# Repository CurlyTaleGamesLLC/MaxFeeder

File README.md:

# Max Feeder

<video autoplay loop muted src="https://user-images.githubusercontent.com/25337335/216802715-1deb94b0-7a2f-4627-93f5-1e41935b5955.mp4">
</video>

## Part Feeding Simplified
### Designed to automate feeding parts for your Open PnP compatible pick and place machine
<br/>

This feeder is designed to be set up as an AutoFeeder in OpenPNP. It easily clips to 2020 aluminum extrusion and uses an Arduino Mega to receive Gcode commands sent over a USB serial connection in Open PnP. The Max Feeder Shield can control up to 34 feeders.

The design of the Max Feeder is based on [the 0816 feeder design from mgrl.](https://docs.mgrl.de/maschine:pickandplace:feeder:0816feeder) However after two years of development I redesigned every piece of it to improve and simplify the feeder as much as possible.

During development, I also referenced the remix of the 0816 feeder made Nicmoly for the Lumen PNP.

<br/>

# Where can I get a Max Feeder?

[I am selling kits of the Max Feeder Shield and kits of 5x 8mm Max Feeders.](https://store.curlytalegames.com/pages/max-feeders)
> The online store is now live! Thanks for supporting this open hardware project!

This is an Open Hardware project, so all of the design files and the BOM are included in this repo as well.

[If you like what I'm doing consider becoming a Github Sponsor :gift_heart:](https://github.com/sponsors/CurlyTaleGames)

<br/>

# Hardware

## Max Feeder Shield
- 1 - Max Feeder Shield PCB
- 34 - 4 Pin 2.54mm JST connectors
- 1 - Arduino Mega
- 1 - 10uf Capacitor
- 1 - Barrel Jack
- 1 - 3.81mm Screw Terminal - Optional
- 1 - 6mm Through Hole Tacticle Switch
- 1 - 5v DC 3A (or more) Power Supply
- LOTS of 2.54mm Male Header
- Mounting Bracket in the "3D" folder

<br/>

## Max Feeder
- 1 - Max Feeder PCB
- 3D printed files in the "3D" folder
- 5 - [M3 6mm screws](https://www.amazon.com/Alloy-Steel-Socket-Screws-Black/dp/B00W8YSCIS/)
- 1 - [4 Pin 2.54mm JST cables 100cm in length ("stepper motor cable")](https://www.amazon.com/Wires-Motor-XH2-54-4P-PH2-0-6P-Printers-Accessories%EF%BC%8C3D/dp/B08PV6XGK2/)
- 3 - [M3 20mm screws](https://www.amazon.com/Prime-Line-9180478-Socket-Screws-10-Pack/dp/B07D5S3154/)
- 1 - [SPDT Limit Switch](https://www.amazon.com/dp/B088W8WMTB)
- 1 - [1N4001 Diode](https://www.amazon.com/MCIGICM-Rectifier-Electronic-Silicon-Doorbell/dp/B071YWNBVM/)
- 1 - [5 pin 2.54mm Angled Male Header](https://www.amazon.com/Antrader-2-54mm-Right-Header-Connector/dp/B07M88GRHG/)
- 1 - [2 pin 2.54mm Female header cable](https://www.amazon.com/Mayata-Female-Jumper-Dupont-Printer/dp/B07H1WDN3R/) or [Female to Female Dupont cables](https://www.amazon.com/EDGELEC-Breadboard-1pin-1pin-Connector-Multicolored/dp/B07GCZVCGS/)
- 1 - [N20 Geared DC Motor 60 RPM](https://www.aliexpress.com/item/3256803042731079.html?pdp_ext_f=%7B"sku_id":"12000024757391447"%7D)
- 1 - [MG90S Servo 180 degree](https://www.amazon.com/Compatible-Raspberry-Project-Helicopter-Airplane/dp/B0925V3X2S/)
- 1 - [M2 14mm dowel pin](https://www.amazon.com/MroMax-2-5x14mm-Stainless-Rust-Proof-Elements/dp/B07ZF4X7VQ/) or [2mm diameter rod cut to 14mm in length](https://www.amazon.com/dp/B0962RMLVJ)
- [Replacement Pen Springs](https://www.amazon.com/dp/B089JYV7BT)
- [Latex Free Orthodontic Elastics](https://www.amazon.com/dp/B08NCK1K6P)

<br/>

# 3D Prints

## Max Feeder

Included are two 3MF files which has all the parts oriented and ready to print. Also there are the individual STL files if your slicer doesn't support 3MF files.

The files that need to be printed with a 0.4mm nozzle are labeled, all the other parts can be printed with 0.4mm, 0.6mm, or 0.8mm nozzles. Everything is designed to be printed without supports. If you print with a 0.8mm nozzle you can print a whole feeder in less than 1.5 hours.

[Download the 8mm Max Feeder.](/3D/8mm/) [12mm](/3D/12mm/), [16mm](/3D/16mm/), and [24mm](/3D/24mm/) versions are available in beta status. All of the feeder widths use the same hardware. The only difference between them are the 3D print files.

### Multiple Mounting Options

`FeederBase.stl` and `FeederCover.stl` are designed to clip onto 2020 aluminum extrusion. This is the default configuration of the Max Feeder and it's designed to mount to the Lumen PnP.

`DIN-FeederBase.stl` and `DIN-FeederCover.stl` are designed to clip onto DIN Rail for pick and place machines with a flat mounting surface, like the LitePlacer.

`2040-FeederBase.stl` and `2040-FeederCover.stl` are designed to clip onto 2040 aluminum extrusion. So it will mount to any pick and place machines that the original 0816 feeder can mount to.

<br/>

## Max Feeder Shield

Included is a bracket to bolt a Max Feeder Shield + Arduino Mega compatible microcontroller to the side of some 2020 aluminum extrusion. The current bracket was designed to be used with a Lumen PNP but might work for other pick and place machines too.

[Download it here](/3D/Bracket/)

<br/>

# Feeder Assembly & Configuration

- [Uploading Firmware](./Docs/firmware.md)
- [Max Feeder PCB Assembly](./Docs/pcb.md)
- [Servo Poker Assembly](./Docs/poker.md)
- [Tape Gear Motor Assembly](./Docs/motor.md)
- [Final Feeder Assembly](./Docs/finishing-assembly.md)
- [Open PnP AutoFeeder Configuration](./Docs/openpnp.md)
- [Loading and Unloading Tape into Max Feeder](./Docs/finishing-assembly.md)

<br/>

## Reel Holder

[Download and print this reel holder for your spools of parts](https://www.printables.com/model/343598-smd-reel-holder-for-pick-and-place-machine)

## Troubleshooting

If you are still having problems after going through the "Feeder Assembly & Configuration" [here are some solutions to common problems](./Docs/troubleshooting.md)

## Notes

There are a few optional parts for the feeder you can print.

### QR Code Cap

This part is attached to the front of your feeder and is designed to have a 1/2" x 1/2" QR code stuck onto it. [Atanisoft](https://github.com/atanisoft) and I have been working on [FeederUtils](https://github.com/atanisoft/FeederUtils), which features a way to import and automatically set up part feeders in Open PnP. The QR code portion of the project is still under development.

[Check it out here](https://github.com/atanisoft/FeederUtils)

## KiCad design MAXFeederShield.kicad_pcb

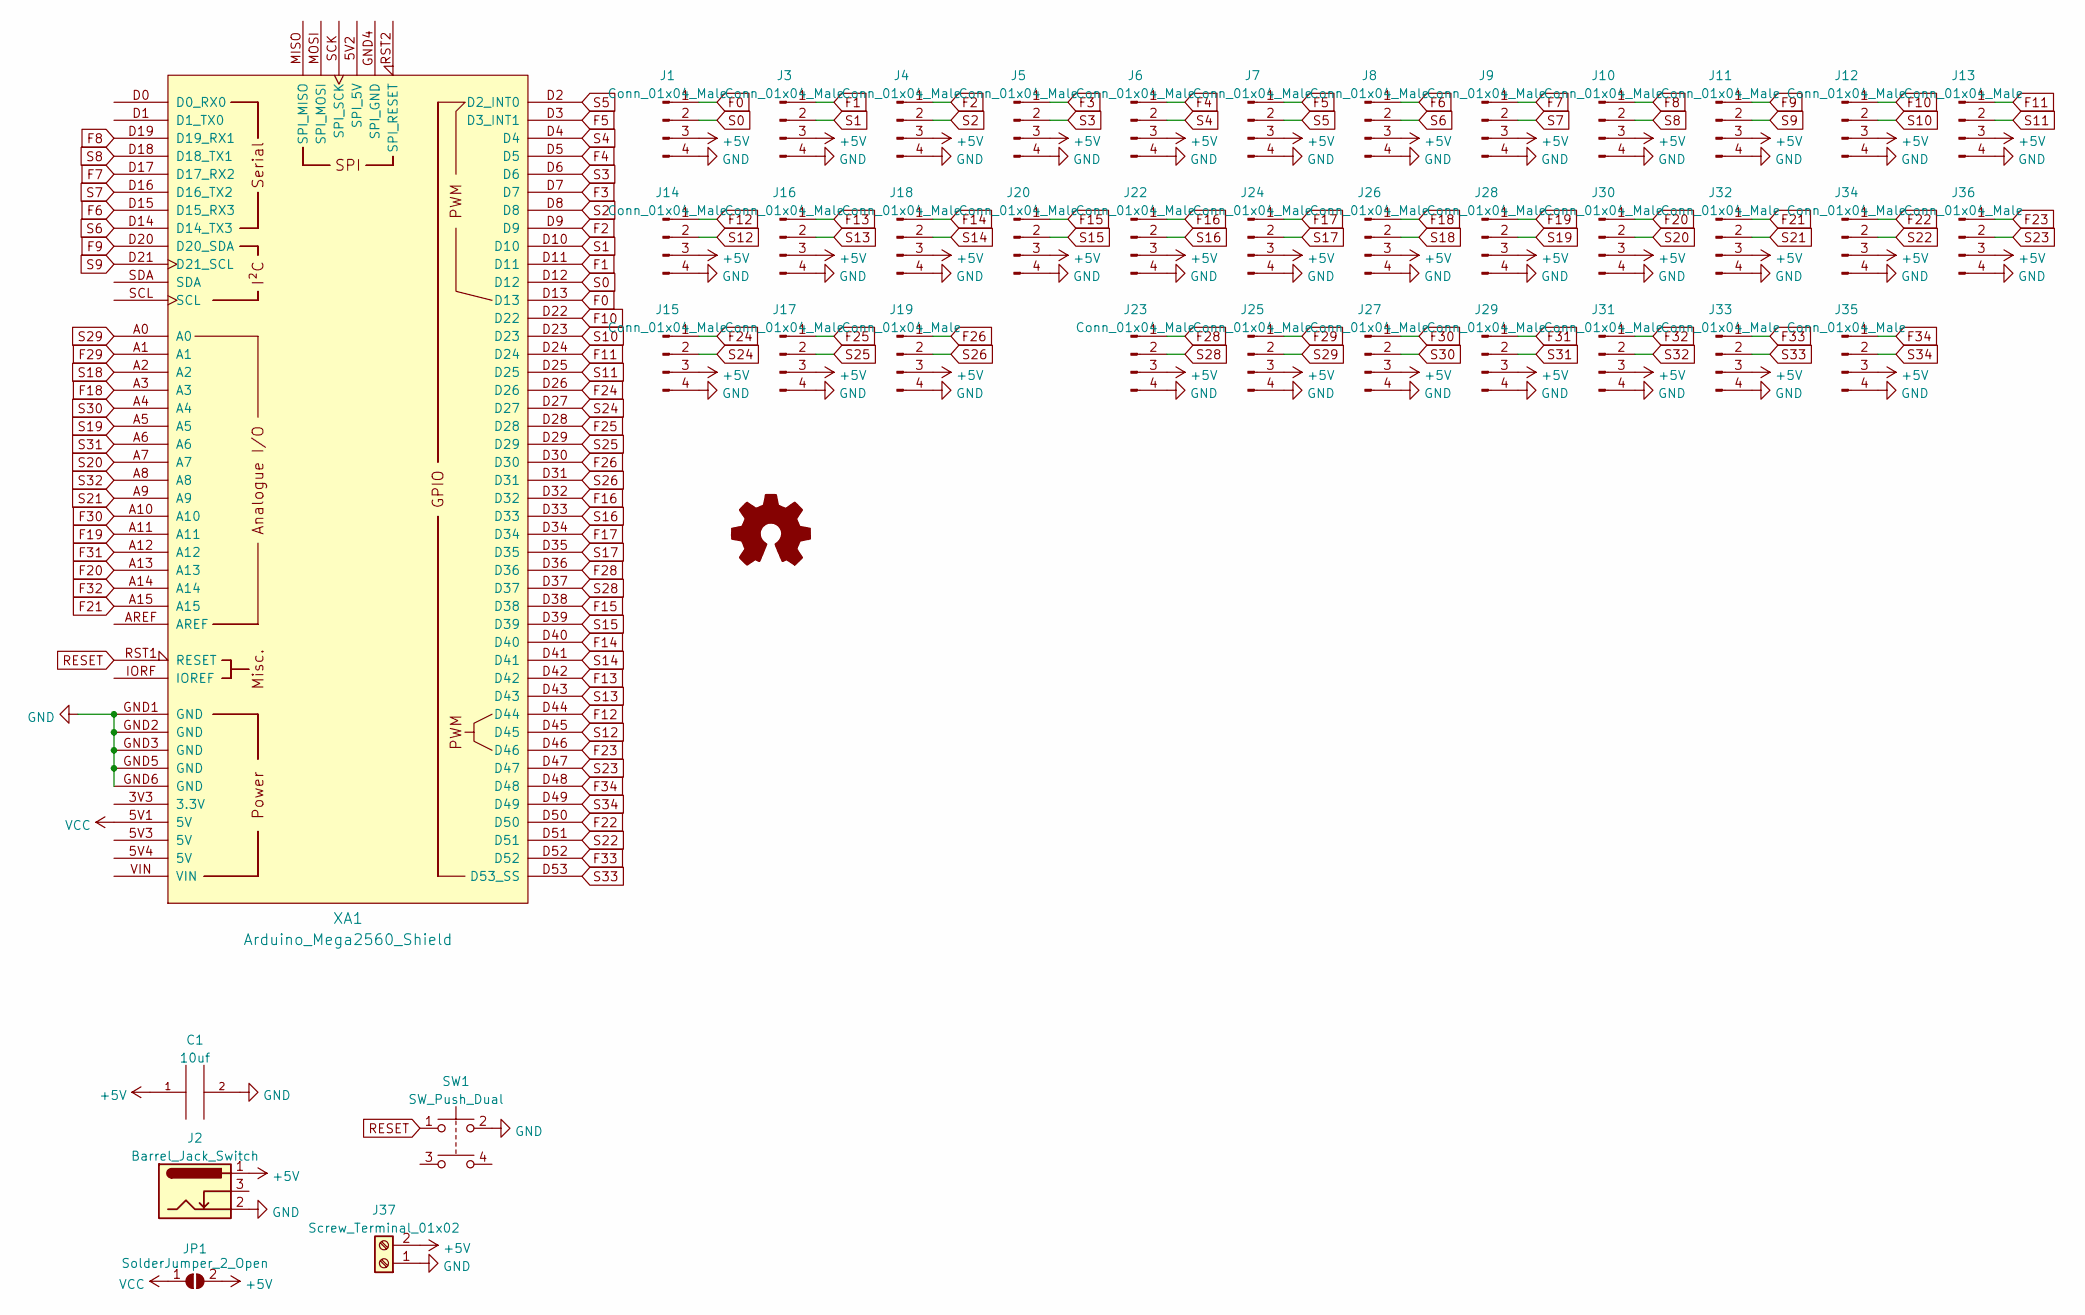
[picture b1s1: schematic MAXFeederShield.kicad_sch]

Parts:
C1: 10uf; CP_Radial_D5.0mm_P2.50mm
J1, J3, J4, J5, J6, J7, J8, J9, J10, J11, J12, J13, J14, J15, J16, J17, J18, J19, J20, J22, J23, J24, J25, J26, J27, J28, J29, J30, J31, J32, J33, J34, J35, J36: Conn_01x04_Male; JST_EH_B4B-EH-A_1x04_P2.50mm_Vertical_LOCKING
J2: Barrel_Jack_Switch; BarrelJack_Horizontal
J37: Screw_Terminal_01x02; PhoenixContact_MC_1,5_2-G-3.81_1x02_P3.81mm_Horizontal
JP1: SolderJumper_2_Open; SolderJumper-2_P1.3mm_Open_Pad1.0x1.5mm
SW1: SW_Push_Dual; SW_PUSH_6mm
XA1: Arduino_Mega2560_Shield; Arduino_Mega2560_Shield_NO_HOLES

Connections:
+5V: C1.1, J1.3, J2.1, J3.3, J4.3, J5.3, J6.3, J7.3, J8.3, J9.3, J10.3, J11.3, J12.3, J13.3, J14.3, J15.3, J16.3, J17.3, J18.3, J19.3, J20.3, J22.3, J23.3, J24.3, J25.3, J26.3, J27.3, J28.3, J29.3, J30.3, J31.3, J32.3, J33.3, J34.3, J35.3, J36.3, J37.2, JP1.2 (B)
F0: J1.1, XA1.D13
F1: J3.1, XA1.D11
F2: J4.1, XA1.D9
F3: J5.1, XA1.D7
F4: J6.1, XA1.D5
F5: J7.1, XA1.D3 (D3_INT1)
F6: J8.1, XA1.D15 (D15_RX3)
F7: J9.1, XA1.D17 (D17_RX2)
F8: J10.1, XA1.D19 (D19_RX1)
F9: J11.1, XA1.D20 (D20_SDA)
F10: J12.1, XA1.D22
F11: J13.1, XA1.D24
F12: J14.1, XA1.D44
F13: J16.1, XA1.D42
F14: J18.1, XA1.D40
F15: J20.1, XA1.D38
F16: J22.1, XA1.D32
F17: J24.1, XA1.D34
F18: J26.1, XA1.A3
F19: J28.1, XA1.A11
F20: J30.1, XA1.A13
F21: J32.1, XA1.A15
F22: J34.1, XA1.D50
F23: J36.1, XA1.D46
F24: J15.1, XA1.D26
F25: J17.1, XA1.D28
F26: J19.1, XA1.D30
F28: J23.1, XA1.D36
F29: J25.1, XA1.A1
F30: J27.1, XA1.A10
F31: J29.1, XA1.A12
F32: J31.1, XA1.A14
F33: J33.1, XA1.D52
F34: J35.1, XA1.D48
GND: C1.2, J1.4, J2.2, J3.4, J4.4, J5.4, J6.4, J7.4, J8.4, J9.4, J10.4, J11.4, J12.4, J13.4, J14.4, J15.4, J16.4, J17.4, J18.4, J19.4, J20.4, J22.4, J23.4, J24.4, J25.4, J26.4, J27.4, J28.4, J29.4, J30.4, J31.4, J32.4, J33.4, J34.4, J35.4, J36.4, J37.1, SW1.2, XA1.GND1 (GND), XA1.GND2 (GND), XA1.GND3 (GND), XA1.GND5 (GND), XA1.GND6 (GND)
RESET: SW1.1, XA1.RST1 (RESET)
S0: J1.2, XA1.D12
S1: J3.2, XA1.D10
S2: J4.2, XA1.D8
S3: J5.2, XA1.D6
S4: J6.2, XA1.D4
S5: J7.2, XA1.D2 (D2_INT0)
S6: J8.2, XA1.D14 (D14_TX3)
S7: J9.2, XA1.D16 (D16_TX2)
S8: J10.2, XA1.D18 (D18_TX1)
S9: J11.2, XA1.D21 (D21_SCL)
S10: J12.2, XA1.D23
S11: J13.2, XA1.D25
S12: J14.2, XA1.D45
S13: J16.2, XA1.D43
S14: J18.2, XA1.D41
S15: J20.2, XA1.D39
S16: J22.2, XA1.D33
S17: J24.2, XA1.D35
S18: J26.2, XA1.A2
S19: J28.2, XA1.A5
S20: J30.2, XA1.A7
S21: J32.2, XA1.A9
S22: J34.2, XA1.D51
S23: J36.2, XA1.D47
S24: J15.2, XA1.D27
S25: J17.2, XA1.D29
S26: J19.2, XA1.D31
S28: J23.2, XA1.D37
S29: J25.2, XA1.A0
S30: J27.2, XA1.A4
S31: J29.2, XA1.A6
S32: J31.2, XA1.A8
S33: J33.2, XA1.D53 (D53_SS)
S34: J35.2, XA1.D49
VCC: JP1.1 (A), XA1.5V1 (5V)

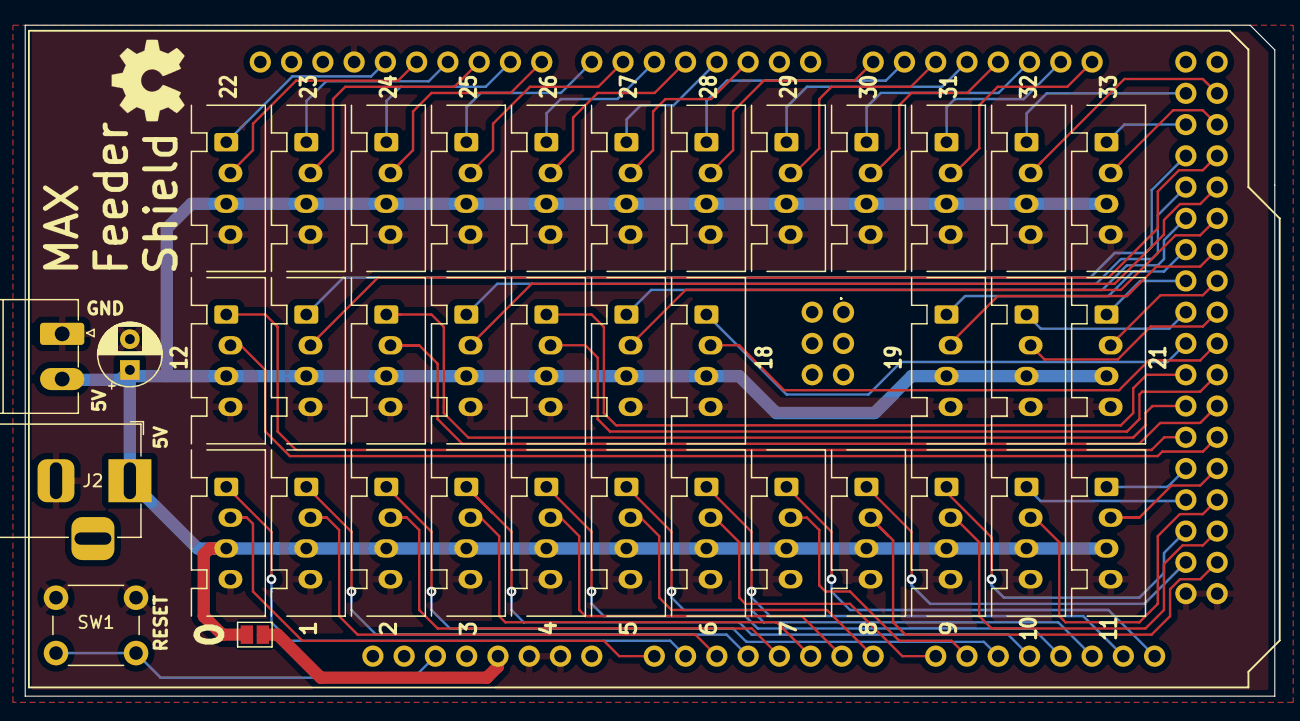
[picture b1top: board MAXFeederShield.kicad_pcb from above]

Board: 2 copper layers, 101.5 x 54.5 mm, 40 parts (0 on the bottom side), 72 nets.

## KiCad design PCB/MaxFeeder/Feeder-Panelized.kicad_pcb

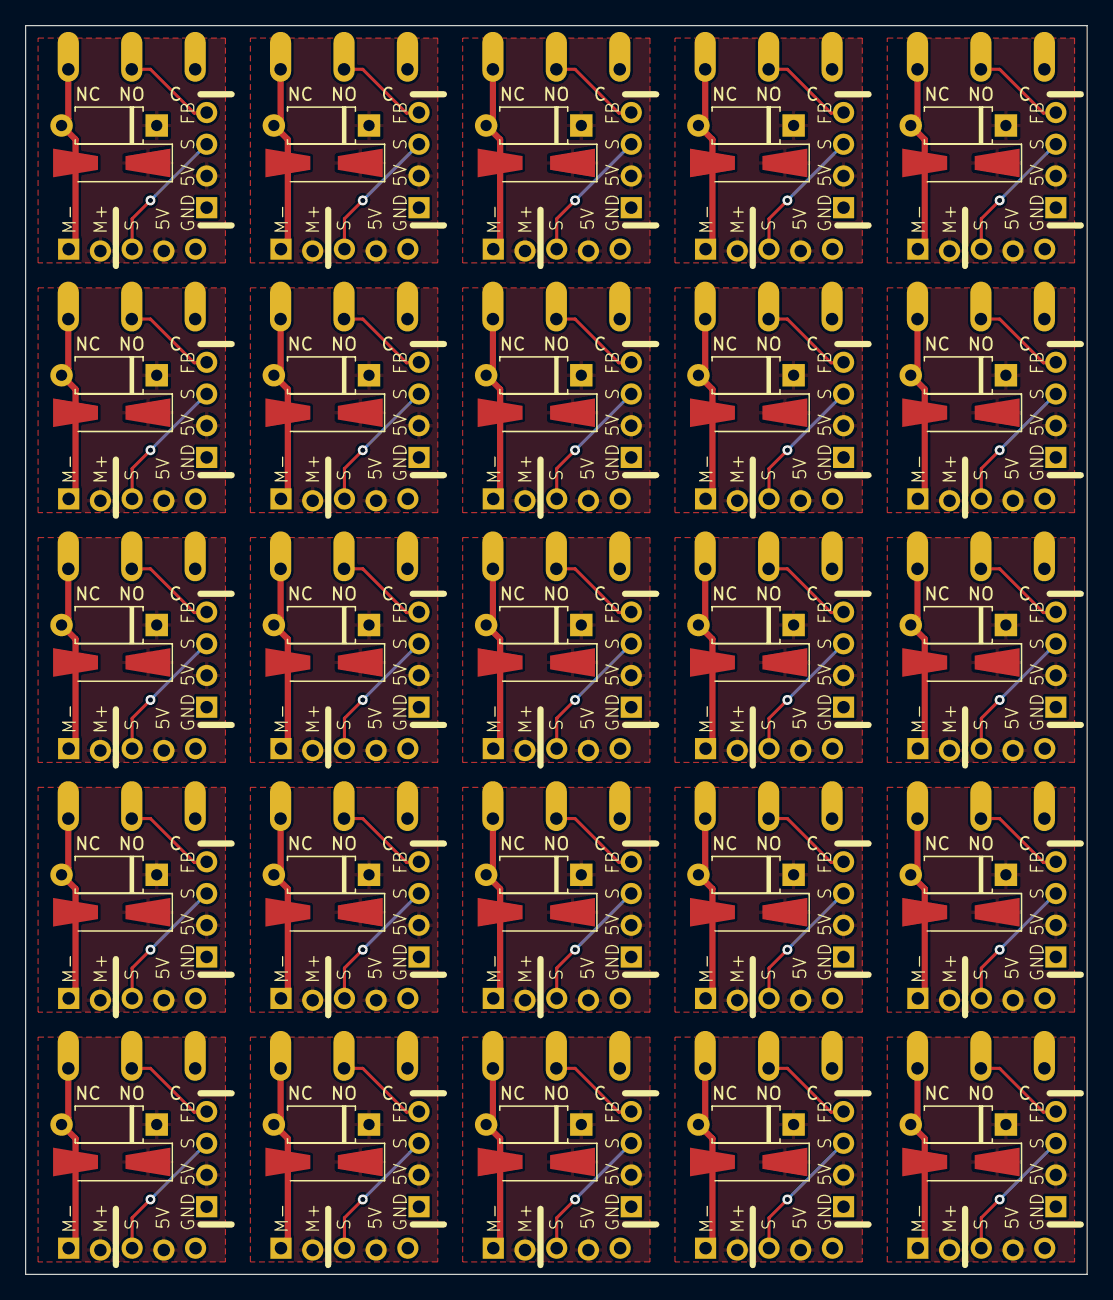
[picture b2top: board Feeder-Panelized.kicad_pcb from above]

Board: 2 copper layers, 85.0 x 100.0 mm, 125 parts (0 on the bottom side), 5 nets.

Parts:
D1, D3, D5, D7, D9, D11, D13, D15, D17, D19, D21, D23, D25, D27, D29, D31, D33, D35, D37, D39, D41, D43, D45, D47, D49: 1N4001; D_SMA-SMB_Universal_Handsoldering
D2, D4, D6, D8, D10, D12, D14, D16, D18, D20, D22, D24, D26, D28, D30, D32, D34, D36, D38, D40, D42, D44, D46, D48, D50: 1N4001; D_A-405_P7.62mm_Horizontal
J1, J2, J3, J7, J9, J11, J13, J15, J17, J19, J21, J23, J25, J27, J29, J31, J33, J35, J37, J39, J41, J43, J45, J47, J49: Conn_01x05; PinSocket_1x05_P2.54mm_Vertical_Clean_Locking
J4, J5, J6, J8, J10, J12, J14, J16, J18, J20, J22, J24, J26, J28, J30, J32, J34, J36, J38, J40, J42, J44, J46, J48, J50: Conn_01x04; PinSocket_1x04_P2.54mm_Vertical_Clean
SW1, SW2, SW3, SW4, SW5, SW6, SW7, SW8, SW9, SW10, SW11, SW12, SW13, SW14, SW15, SW16, SW17, SW18, SW19, SW20, SW21, SW22, SW23, SW24, SW25: SW_SPDT; Microswitch

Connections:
+5V: D1.1 (K), D2.1 (K), D3.1 (K), D4.1 (K), D5.1 (K), D6.1 (K), D7.1 (K), D8.1 (K), D9.1 (K), D10.1 (K), D11.1 (K), D12.1 (K), D13.1 (K), D14.1 (K), D15.1 (K), D16.1 (K), D17.1 (K), D18.1 (K), D19.1 (K), D20.1 (K), D21.1 (K), D22.1 (K), D23.1 (K), D24.1 (K), D25.1 (K), D26.1 (K), D27.1 (K), D28.1 (K), D29.1 (K), D30.1 (K), D31.1 (K), D32.1 (K), D33.1 (K), D34.1 (K), D35.1 (K), D36.1 (K), D37.1 (K), D38.1 (K), D39.1 (K), D40.1 (K), D41.1 (K), D42.1 (K), D43.1 (K), D44.1 (K), D45.1 (K), D46.1 (K), D47.1 (K), D48.1 (K), D49.1 (K), D50.1 (K), J1.2, J1.4, J2.2, J2.4, J3.2, J3.4, J4.2, J5.2, J6.2, J7.2, J7.4, J8.2, J9.2, J9.4, J10.2, J11.2, J11.4, J12.2, J13.2, J13.4, J14.2, J15.2, J15.4, J16.2, J17.2, J17.4, J18.2, J19.2, J19.4, J20.2, J21.2, J21.4, J22.2, J23.2, J23.4, J24.2, J25.2, J25.4, J26.2, J27.2, J27.4, J28.2, J29.2, J29.4, J30.2, J31.2, J31.4, J32.2, J33.2, J33.4, J34.2, J35.2, J35.4, J36.2, J37.2, J37.4, J38.2, J39.2, J39.4, J40.2, J41.2, J41.4, J42.2, J43.2, J43.4, J44.2, J45.2, J45.4, J46.2, J47.2, J47.4, J48.2, J49.2, J49.4, J50.2
/FEEDBACK: J4.4, J5.4, J6.4, J8.4, J10.4, J12.4, J14.4, J16.4, J18.4, J20.4, J22.4, J24.4, J26.4, J28.4, J30.4, J32.4, J34.4, J36.4, J38.4, J40.4, J42.4, J44.4, J46.4, J48.4, J50.4, SW1.3 (C), SW2.3 (C), SW3.3 (C), SW4.3 (C), SW5.3 (C), SW6.3 (C), SW7.3 (C), SW8.3 (C), SW9.3 (C), SW10.3 (C), SW11.3 (C), SW12.3 (C), SW13.3 (C), SW14.3 (C), SW15.3 (C), SW16.3 (C), SW17.3 (C), SW18.3 (C), SW19.3 (C), SW20.3 (C), SW21.3 (C), SW22.3 (C), SW23.3 (C), SW24.3 (C), SW25.3 (C)
/N20-GND: D1.2 (A), D2.2 (A), D3.2 (A), D4.2 (A), D5.2 (A), D6.2 (A), D7.2 (A), D8.2 (A), D9.2 (A), D10.2 (A), D11.2 (A), D12.2 (A), D13.2 (A), D14.2 (A), D15.2 (A), D16.2 (A), D17.2 (A), D18.2 (A), D19.2 (A), D20.2 (A), D21.2 (A), D22.2 (A), D23.2 (A), D24.2 (A), D25.2 (A), D26.2 (A), D27.2 (A), D28.2 (A), D29.2 (A), D30.2 (A), D31.2 (A), D32.2 (A), D33.2 (A), D34.2 (A), D35.2 (A), D36.2 (A), D37.2 (A), D38.2 (A), D39.2 (A), D40.2 (A), D41.2 (A), D42.2 (A), D43.2 (A), D44.2 (A), D45.2 (A), D46.2 (A), D47.2 (A), D48.2 (A), D49.2 (A), D50.2 (A), J1.1, J2.1, J3.1, J7.1, J9.1, J11.1, J13.1, J15.1, J17.1, J19.1, J21.1, J23.1, J25.1, J27.1, J29.1, J31.1, J33.1, J35.1, J37.1, J39.1, J41.1, J43.1, J45.1, J47.1, J49.1, SW1.1 (A), SW2.1 (A), SW3.1 (A), SW4.1 (A), SW5.1 (A), SW6.1 (A), SW7.1 (A), SW8.1 (A), SW9.1 (A), SW10.1 (A), SW11.1 (A), SW12.1 (A), SW13.1 (A), SW14.1 (A), SW15.1 (A), SW16.1 (A), SW17.1 (A), SW18.1 (A), SW19.1 (A), SW20.1 (A), SW21.1 (A), SW22.1 (A), SW23.1 (A), SW24.1 (A), SW25.1 (A)
/SERVO: J1.3, J2.3, J3.3, J4.3, J5.3, J6.3, J7.3, J8.3, J9.3, J10.3, J11.3, J12.3, J13.3, J14.3, J15.3, J16.3, J17.3, J18.3, J19.3, J20.3, J21.3, J22.3, J23.3, J24.3, J25.3, J26.3, J27.3, J28.3, J29.3, J30.3, J31.3, J32.3, J33.3, J34.3, J35.3, J36.3, J37.3, J38.3, J39.3, J40.3, J41.3, J42.3, J43.3, J44.3, J45.3, J46.3, J47.3, J48.3, J49.3, J50.3
GND: J1.5, J2.5, J3.5, J4.1, J5.1, J6.1, J7.5, J8.1, J9.5, J10.1, J11.5, J12.1, J13.5, J14.1, J15.5, J16.1, J17.5, J18.1, J19.5, J20.1, J21.5, J22.1, J23.5, J24.1, J25.5, J26.1, J27.5, J28.1, J29.5, J30.1, J31.5, J32.1, J33.5, J34.1, J35.5, J36.1, J37.5, J38.1, J39.5, J40.1, J41.5, J42.1, J43.5, J44.1, J45.5, J46.1, J47.5, J48.1, J49.5, J50.1, SW1.2 (B), SW2.2 (B), SW3.2 (B), SW4.2 (B), SW5.2 (B), SW6.2 (B), SW7.2 (B), SW8.2 (B), SW9.2 (B), SW10.2 (B), SW11.2 (B), SW12.2 (B), SW13.2 (B), SW14.2 (B), SW15.2 (B), SW16.2 (B), SW17.2 (B), SW18.2 (B), SW19.2 (B), SW20.2 (B), SW21.2 (B), SW22.2 (B), SW23.2 (B), SW24.2 (B), SW25.2 (B)

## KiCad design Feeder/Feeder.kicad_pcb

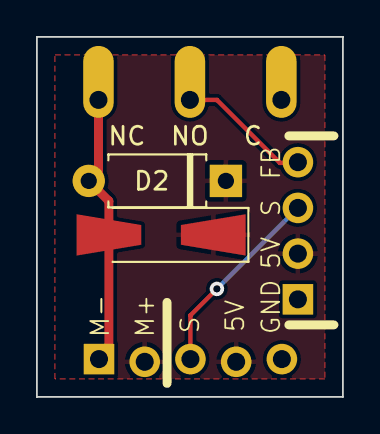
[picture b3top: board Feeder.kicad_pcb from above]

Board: 2 copper layers, 17.0 x 20.0 mm, 5 parts (0 on the bottom side), 5 nets.

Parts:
D1: 1N4001; D_SMA-SMB_Universal_Handsoldering
D2: 1N4001; D_A-405_P7.62mm_Horizontal
J1: Conn_01x05; PinSocket_1x05_P2.54mm_Vertical_Clean_Locking
J4: Conn_01x04; PinSocket_1x04_P2.54mm_Vertical_Clean
SW1: SW_SPDT; Microswitch

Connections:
+5V: D1.1 (K), D2.1 (K), J1.2, J1.4, J4.2
/FEEDBACK: J4.4, SW1.3 (C)
/N20-GND: D1.2 (A), D2.2 (A), J1.1, SW1.1 (A)
/SERVO: J1.3, J4.3
GND: J1.5, J4.1, SW1.2 (B)

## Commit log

2022-05-19 hello world!
2022-07-01 Redesigned shield PCB, as well as adapter PCB, modified 0816 feeder firmware
2022-07-01 fixed some file names and updated readme
2022-07-12 tweaked pad size on PCB and added 3d files for 8mm feeder
2022-07-12 fixed 3d model, updated docs
2022-07-14 added correct 3d gear part, added pictures, and fixed typo
2022-07-17 updated feeder design and documentation
2022-07-19 added 0.1mm to gear axle diameter thinned QR mounting point to snap on, and added links to docs
2022-11-20 removed need for M610 S1 command, auto detach servos
2023-01-18 updated 3d files, updated docs, added validation script
2023-01-18 added bracket step file
2023-01-30 Added more clearance for thicker 8mm paper tape, and adjusted leaf spring to also work better with thinner plastic tapes
2023-02-02 added updated documentation - updated max feeder shield bracket
2023-02-02 typo, added video
2023-02-04 fixed docs, updated leaf spring
2023-02-05 added docs for open pnp
2023-02-05 updated front page readme, added error regex
2023-02-05 added notes to readme
2023-03-28 launched online store
2023-04-16 added beta 12mm feeders and added pro tip to motor gears
2023-09-11 python script to test the feeders
2023-09-11 fix the window title
2023-09-11 fix the script to support 34 feeders
2023-09-12 add keyboard shortkut function and F value for each feeder controlled
2023-09-12 deleting keyboar assignation on second click
2023-09-12 key not monitored when the app is not in focus
2023-09-12 add readme
2023-09-12 add the port name in the serial status label add serial open condition for writing and listening
2023-11-05 Added PCB poker tip, added 8-24mm feeder widths, updated docs, cleaned up repo
2023-11-05 added reel holder link
2023-11-05 added photo of pcb poker tips
2023-11-07 forgot to include the washer in the plate, updated the 24mm base leaf spring to have more contact with bed
2023-11-16 added support for DIN rail mounted feeders for liteplacer. Updated leaf spring for more reliable printing
2023-12-03 added 2040 max feeder version, fixed hole diameter in base, thicker leaf spring to easier printing
2024-02-10 removed unique part number silk screen on diodes
2025-01-28 smoothed out servo movements, trying to fix some parts being ejected from the tape
2025-02-01 switched smooth angle function to only be used during retractions
